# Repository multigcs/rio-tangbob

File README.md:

# TangBOB

cheap universal-board for LinuxCNC-RIO

* W5500
* Level-Shifter (TXS0108E)
* RGB-LED
* Modbus
* I2C - 5V (hope this will work via the level-shifter)

Kicad-Footprint for the TangNano9K:

    https://github.com/jabadiagm/MSXmapper_tn9k/tree/main/kicad/t_mapper.pretty

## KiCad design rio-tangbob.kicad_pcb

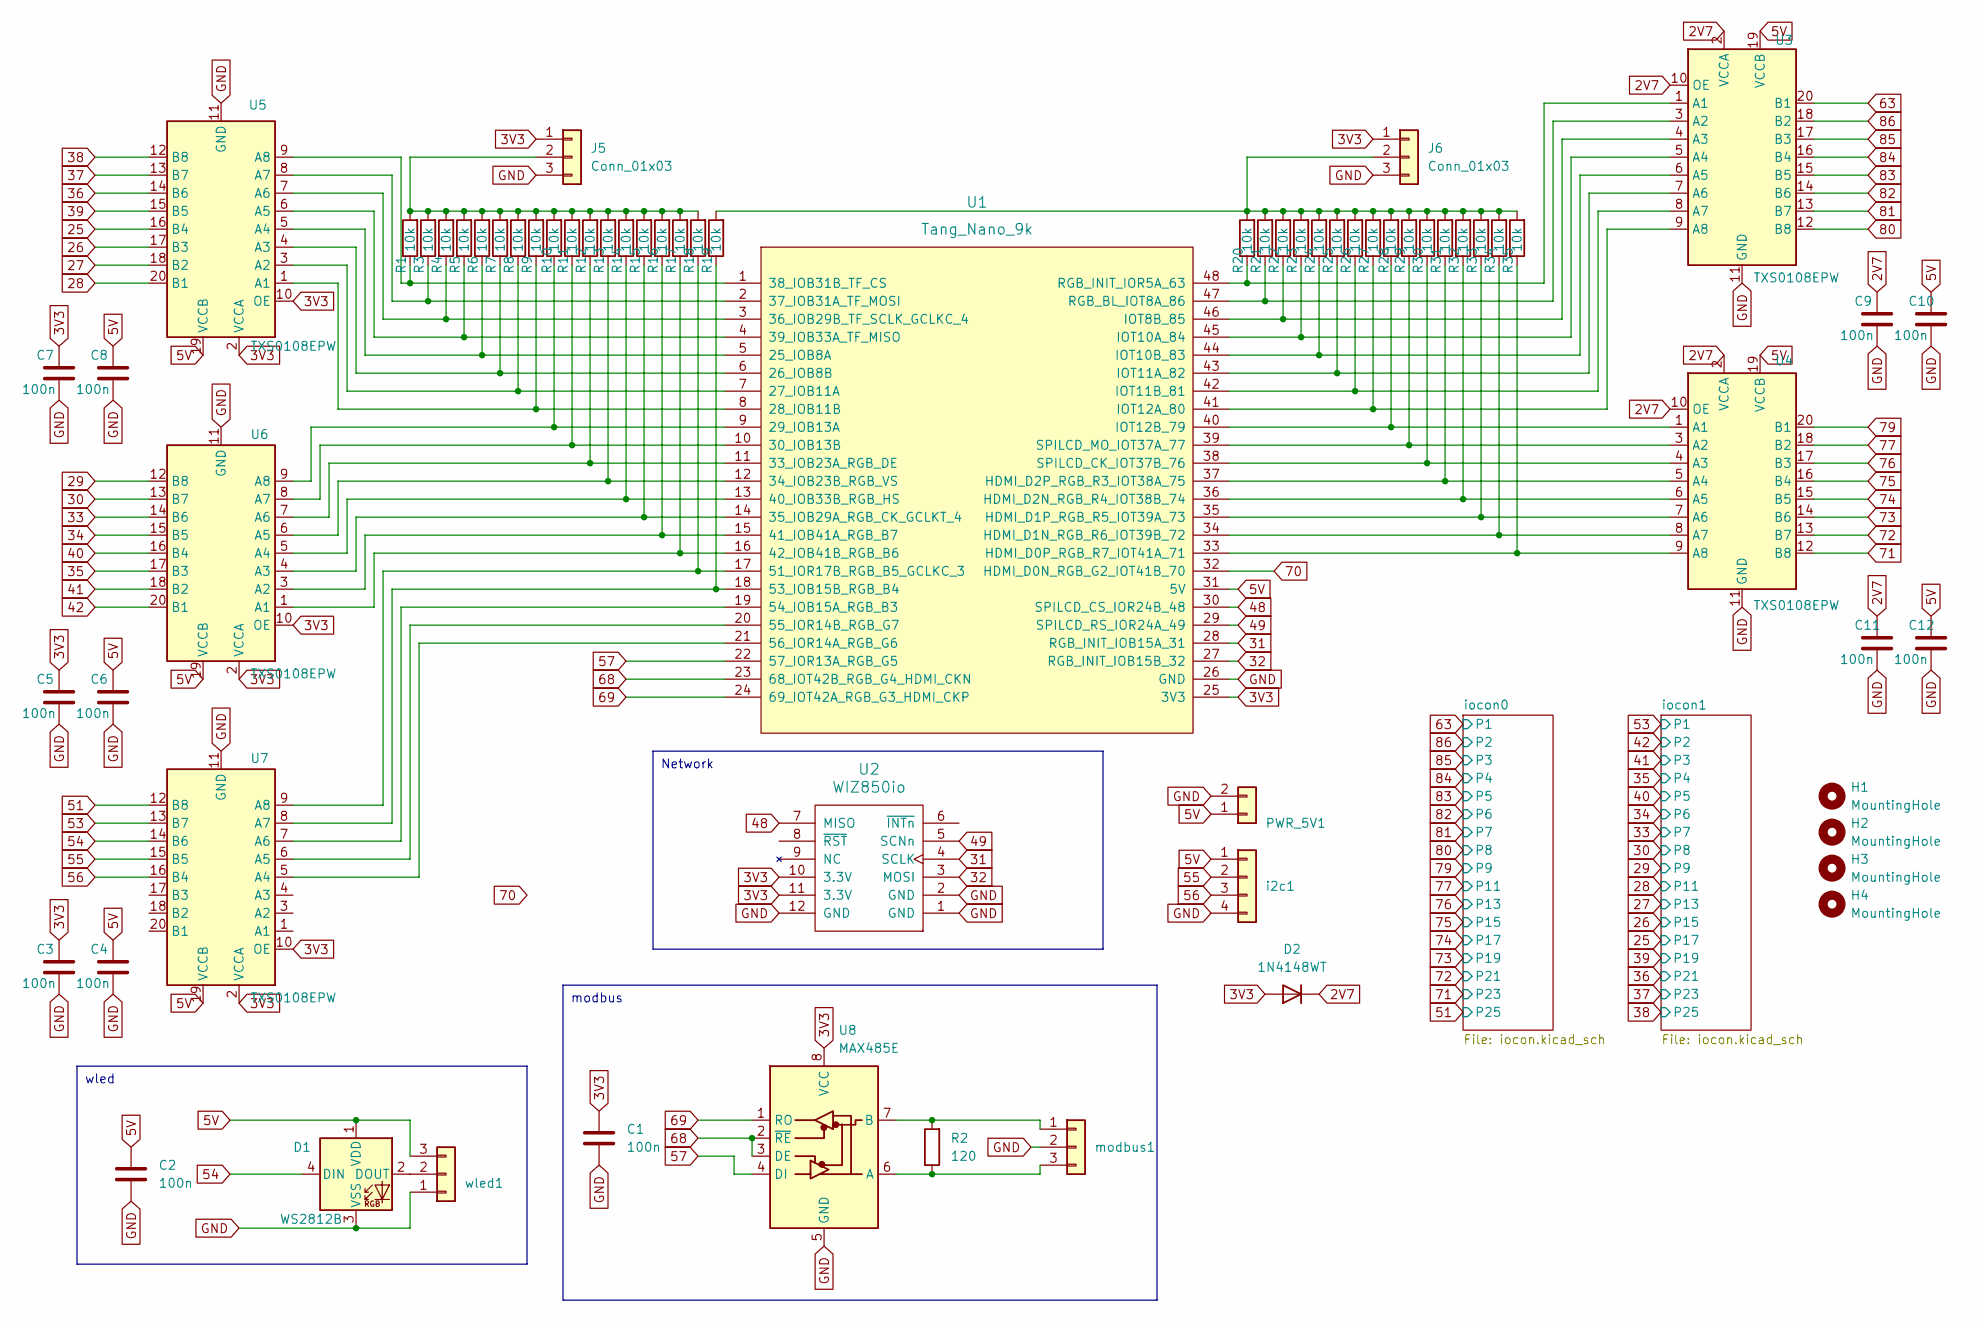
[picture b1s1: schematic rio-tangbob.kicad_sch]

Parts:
C1, C2, C3, C4, C5, C6, C7, C8, C9, C10, C11, C12: 100n; C_1206_3216Metric
D1: WS2812B; LED_WS2812B_PLCC4_5.0x5.0mm_P3.2mm
D2: 1N4148WT; D_SOD-523
H1, H2, H3, H4: MountingHole; MountingHole_3.2mm_M3_DIN965
J5, J6: Conn_01x03; PinHeader_1x03_P2.54mm_Vertical
PWR_5V1: Conn_01x03; JST_XH_B2B-XH-A_1x02_P2.50mm_Vertical
R1, R3, R4, R5, R6, R7, R8, R9, R10, R11, R12, R13, R14, R15, R16, R17, R18, R19, R20, R21, R22, R23, R24, R25, R26, R27, R28, R29, R30, R31, R32, R33, R34, R35: 10k; R_1206_3216Metric
R2: 120; R_1206_3216Metric
U1: Tang_Nano_9k
U2: WIZ850io
U3, U4, U5, U6, U7: TXS0108EPW; TSSOP-20_4.4x6.5mm_P0.65mm
U8: MAX485E; Diodes_SO-8EP
i2c1: Conn_01x03; JST_XH_B4B-XH-A_1x04_P2.50mm_Vertical
modbus1: Conn_01x03; JST_XH_B3B-XH-A_1x03_P2.50mm_Vertical
wled1: Conn_01x03; JST_XH_B3B-XH-A_1x03_P2.50mm_Vertical

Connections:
2V7: C9.1, C11.1, D2.1 (K), U3.2 (VCCA), U3.10 (OE), U4.2 (VCCA), U4.10 (OE)
3V3: C1.1, C3.1, C5.1, C7.1, D2.2 (A), J5.1, J6.1, U1.25 (3V3), U2.10 (3.3V), U2.11 (3.3V), U5.2 (VCCA), U5.10 (OE), U6.2 (VCCA), U6.10 (OE), U7.2 (VCCA), U7.10 (OE), U8.8 (VCC)
5V: C2.1, C4.1, C6.1, C8.1, C10.1, C12.1, D1.1 (VDD), PWR_5V1.1, U1.31 (5V), U3.19 (VCCB), U4.19 (VCCB), U5.19 (VCCB), U6.19 (VCCB), U7.19 (VCCB), i2c1.1, wled1.3; also elsewhere on the board
25: U5.16 (B4); also elsewhere on the board
26: U5.17 (B3); also elsewhere on the board
27: U5.18 (B2); also elsewhere on the board
28: U5.20 (B1); also elsewhere on the board
29: U6.12 (B8); also elsewhere on the board
30: U6.13 (B7); also elsewhere on the board
31: U1.28 (RGB_INIT_IOB15A_31), U2.4 (SCLK)
32: U1.27 (RGB_INIT_IOB15B_32), U2.3 (MOSI)
33: U6.14 (B6); also elsewhere on the board
34: U6.15 (B5); also elsewhere on the board
35: U6.17 (B3); also elsewhere on the board
36: U5.14 (B6); also elsewhere on the board
37: U5.13 (B7); also elsewhere on the board
38: U5.12 (B8); also elsewhere on the board
39: U5.15 (B5); also elsewhere on the board
40: U6.16 (B4); also elsewhere on the board
41: U6.18 (B2); also elsewhere on the board
42: U6.20 (B1); also elsewhere on the board
48: U1.30 (SPILCD_CS_IOR24B_48), U2.7 (MISO)
49: U1.29 (SPILCD_RS_IOR24A_49), U2.5 (SCNn)
51: U7.12 (B8); also elsewhere on the board
53: U7.13 (B7); also elsewhere on the board
54: D1.4 (DIN), U7.14 (B6)
55: U7.15 (B5), i2c1.2
56: U7.16 (B4), i2c1.3
57: U1.22 (57_IOR13A_RGB_G5), U8.4 (DI)
63: U3.20 (B1); also elsewhere on the board
68: U1.23 (68_IOT42B_RGB_G4_HDMI_CKN), U8.2 (~RE), U8.3 (DE)
69: U1.24 (69_IOT42A_RGB_G3_HDMI_CKP), U8.1 (RO)
70: U1.32 (HDMI_D0N_RGB_G2_IOT41B_70)
71: U4.12 (B8); also elsewhere on the board
72: U4.13 (B7); also elsewhere on the board
73: U4.14 (B6); also elsewhere on the board
74: U4.15 (B5); also elsewhere on the board
75: U4.16 (B4); also elsewhere on the board
76: U4.17 (B3); also elsewhere on the board
77: U4.18 (B2); also elsewhere on the board
79: U4.20 (B1); also elsewhere on the board
80: U3.12 (B8); also elsewhere on the board
81: U3.13 (B7); also elsewhere on the board
82: U3.14 (B6); also elsewhere on the board
83: U3.15 (B5); also elsewhere on the board
84: U3.16 (B4); also elsewhere on the board
85: U3.17 (B3); also elsewhere on the board
86: U3.18 (B2); also elsewhere on the board
GND: C1.2, C2.2, C3.2, C4.2, C5.2, C6.2, C7.2, C8.2, C9.2, C10.2, C11.2, C12.2, D1.3 (VSS), J5.3, J6.3, PWR_5V1.2, U1.26 (GND), U2.1 (GND), U2.2 (GND), U2.12 (GND), U3.11 (GND), U4.11 (GND), U5.11 (GND), U6.11 (GND), U7.11 (GND), U8.5 (GND), i2c1.4, modbus1.2, wled1.1; also elsewhere on the board
unnamed: D1.2 (DOUT), wled1.2
unnamed: J5.2, R1.2, R3.2, R4.2, R5.2, R6.2, R7.2, R8.2, R9.2, R10.2, R11.2, R12.2, R13.2, R14.2, R15.2, R16.2, R17.2, R18.2
unnamed: J6.2, R19.2, R20.2, R21.2, R22.2, R23.2, R24.2, R25.2, R26.2, R27.2, R28.2, R29.2, R30.2, R31.2, R32.2, R33.2, R34.2, R35.2
unnamed: R6.1, U1.5 (25_IOB8A), U5.5 (A4)
unnamed: R7.1, U1.6 (26_IOB8B), U5.4 (A3)
unnamed: R8.1, U1.7 (27_IOB11A), U5.3 (A2)
unnamed: R9.1, U1.8 (28_IOB11B), U5.1 (A1)
unnamed: R10.1, U1.9 (29_IOB13A), U6.9 (A8)
unnamed: R11.1, U1.10 (30_IOB13B), U6.8 (A7)
unnamed: R12.1, U1.11 (33_IOB23A_RGB_DE), U6.7 (A6)
unnamed: R13.1, U1.12 (34_IOB23B_RGB_VS), U6.6 (A5)
unnamed: R15.1, U1.14 (35_IOB29A_RGB_CK_GCLKT_4), U6.4 (A3)
unnamed: R4.1, U1.3 (36_IOB29B_TF_SCLK_GCLKC_4), U5.7 (A6)
unnamed: R3.1, U1.2 (37_IOB31A_TF_MOSI), U5.8 (A7)
unnamed: R1.1, U1.1 (38_IOB31B_TF_CS), U5.9 (A8)
unnamed: R5.1, U1.4 (39_IOB33A_TF_MISO), U5.6 (A5)
unnamed: R14.1, U1.13 (40_IOB33B_RGB_HS), U6.5 (A4)
unnamed: R16.1, U1.15 (41_IOB41A_RGB_B7), U6.3 (A2)
unnamed: R17.1, U1.16 (42_IOB41B_RGB_B6), U6.1 (A1)
unnamed: R18.1, U1.17 (51_IOR17B_RGB_B5_GCLKC_3), U7.9 (A8)
unnamed: R19.1, U1.18 (53_IOB15B_RGB_B4), U7.8 (A7)
unnamed: U1.19 (54_IOB15A_RGB_B3), U7.7 (A6)
unnamed: U1.20 (55_IOR14B_RGB_G7), U7.6 (A5)
unnamed: U1.21 (56_IOR14A_RGB_G6), U7.5 (A4)
unnamed: R35.1, U1.33 (HDMI_D0P_RGB_R7_IOT41A_71), U4.9 (A8)
unnamed: R34.1, U1.34 (HDMI_D1N_RGB_R6_IOT39B_72), U4.8 (A7)
unnamed: R33.1, U1.35 (HDMI_D1P_RGB_R5_IOT39A_73), U4.7 (A6)
unnamed: R32.1, U1.36 (HDMI_D2N_RGB_R4_IOT38B_74), U4.6 (A5)
unnamed: R31.1, U1.37 (HDMI_D2P_RGB_R3_IOT38A_75), U4.5 (A4)
unnamed: R22.1, U1.46 (IOT8B_85), U3.4 (A3)
unnamed: R23.1, U1.45 (IOT10A_84), U3.5 (A4)
unnamed: R24.1, U1.44 (IOT10B_83), U3.6 (A5)
unnamed: R25.1, U1.43 (IOT11A_82), U3.7 (A6)
unnamed: R26.1, U1.42 (IOT11B_81), U3.8 (A7)
unnamed: R27.1, U1.41 (IOT12A_80), U3.9 (A8)
unnamed: R28.1, U1.40 (IOT12B_79), U4.1 (A1)
unnamed: R21.1, U1.47 (RGB_BL_IOT8A_86), U3.3 (A2)
unnamed: R20.1, U1.48 (RGB_INIT_IOR5A_63), U3.1 (A1)
unnamed: R30.1, U1.38 (SPILCD_CK_IOT37B_76), U4.4 (A3)
unnamed: R29.1, U1.39 (SPILCD_MO_IOT37A_77), U4.3 (A2)
unnamed: R2.1, U8.6 (A), modbus1.3
unnamed: R2.2, U8.7 (B), modbus1.1

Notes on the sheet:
modbus
wled
Network

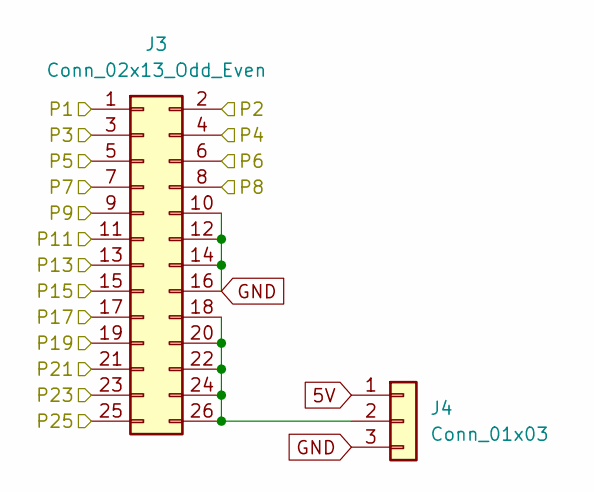
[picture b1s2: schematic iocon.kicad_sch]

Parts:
J3: Conn_02x13_Odd_Even; IDC-Header_2x13_P2.54mm_Vertical
J4: Conn_01x03; PinHeader_1x03_P2.54mm_Vertical

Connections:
5V: J4.1; also elsewhere on the board
25: J3.17; also elsewhere on the board
26: J3.15; also elsewhere on the board
27: J3.13; also elsewhere on the board
28: J3.11; also elsewhere on the board
29: J3.9; also elsewhere on the board
30: J3.8; also elsewhere on the board
33: J3.7; also elsewhere on the board
34: J3.6; also elsewhere on the board
35: J3.4; also elsewhere on the board
36: J3.21; also elsewhere on the board
37: J3.23; also elsewhere on the board
38: J3.25; also elsewhere on the board
39: J3.19; also elsewhere on the board
40: J3.5; also elsewhere on the board
41: J3.3; also elsewhere on the board
42: J3.2; also elsewhere on the board
53: J3.1; also elsewhere on the board
GND: J3.10, J3.12, J3.14, J3.16, J4.3; also elsewhere on the board
unnamed: J3.18, J3.20, J3.22, J3.24, J3.26, J4.2

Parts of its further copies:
J1: Conn_02x13_Odd_Even; IDC-Header_2x13_P2.54mm_Vertical
J2: Conn_01x03; PinHeader_1x03_P2.54mm_Vertical

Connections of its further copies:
5V: J2.1; also elsewhere on the board
51: J1.25; also elsewhere on the board
63: J1.1; also elsewhere on the board
71: J1.23; also elsewhere on the board
72: J1.21; also elsewhere on the board
73: J1.19; also elsewhere on the board
74: J1.17; also elsewhere on the board
75: J1.15; also elsewhere on the board
76: J1.13; also elsewhere on the board
77: J1.11; also elsewhere on the board
79: J1.9; also elsewhere on the board
80: J1.8; also elsewhere on the board
81: J1.7; also elsewhere on the board
82: J1.6; also elsewhere on the board
83: J1.5; also elsewhere on the board
84: J1.4; also elsewhere on the board
85: J1.3; also elsewhere on the board
86: J1.2; also elsewhere on the board
GND: J1.10, J1.12, J1.14, J1.16, J2.3; also elsewhere on the board
unnamed: J1.18, J1.20, J1.22, J1.24, J1.26, J2.2

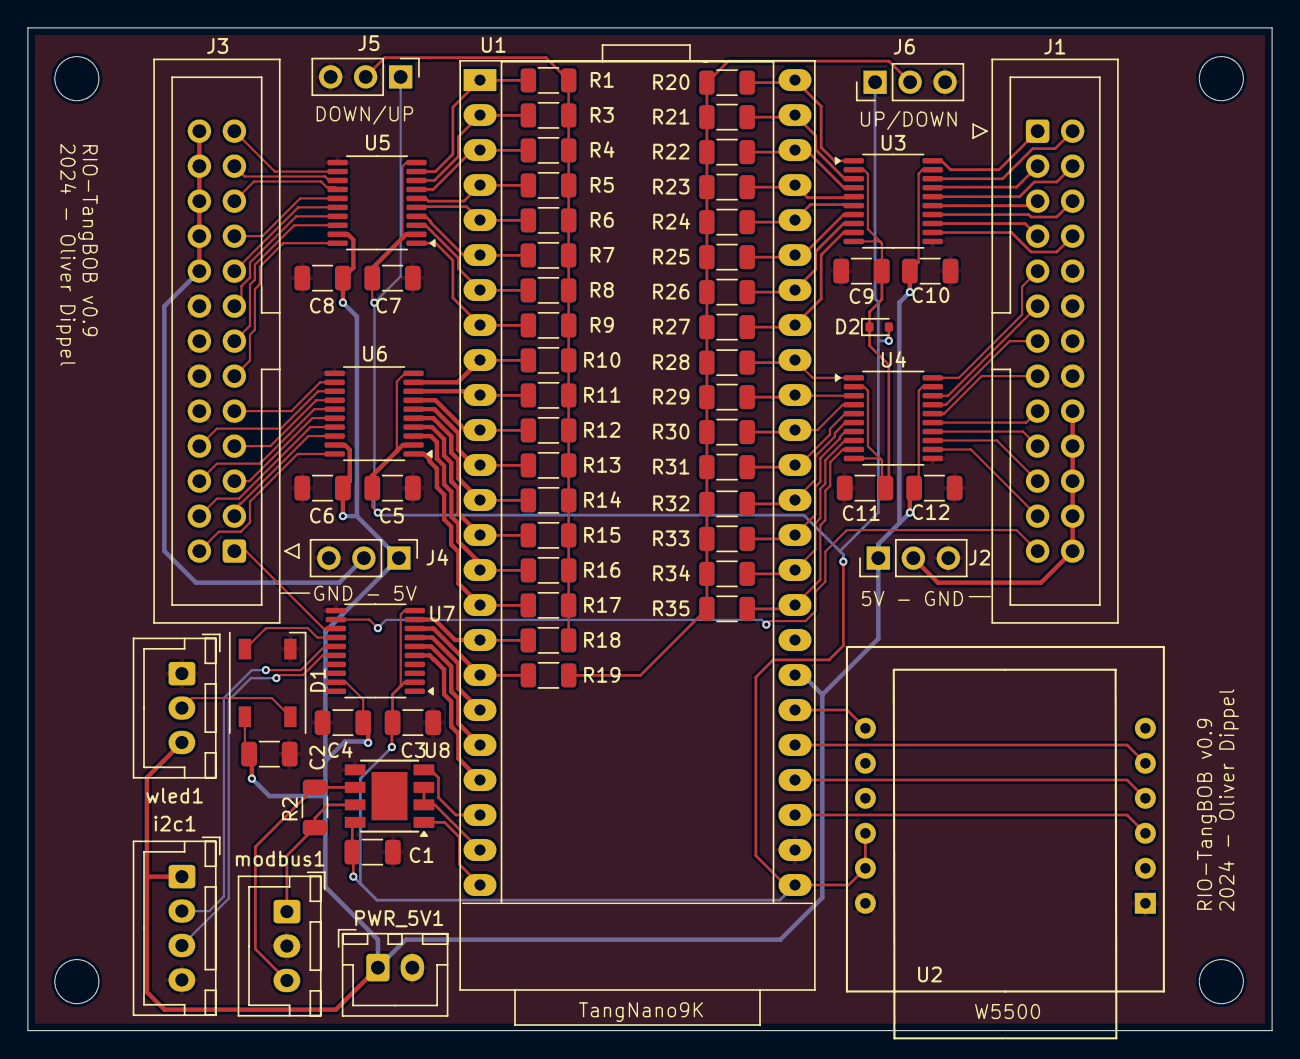
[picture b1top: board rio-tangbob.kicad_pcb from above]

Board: 2 copper layers, 90.3 x 72.8 mm, 71 parts (0 on the bottom side), 92 nets.

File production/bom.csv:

Designator,Footprint,Quantity,Value,LCSC Part #
"C1, C10, C11, C12, C2, C3, C4, C5, C6, C7, C8, C9",1206,12,100n,
D1,LED_WS2812B_PLCC4_5.0x5.0mm_P3.2mm,1,WS2812B,
D2,D_SOD-523,1,1N4148WT,
I2C1,JST_XH_B4B-XH-A_1x04_P2.50mm_Vertical,1,Conn_01x03,
"J1, J3",IDC-Header_2x13_P2.54mm_Vertical,2,Conn_02x13_Odd_Even,
"J2, J4, J5, J6",PinHeader_1x03_P2.54mm_Vertical,4,Conn_01x03,
"MODBUS1, WLED1",JST_XH_B3B-XH-A_1x03_P2.50mm_Vertical,2,Conn_01x03,
PWR_5V1,JST_XH_B2B-XH-A_1x02_P2.50mm_Vertical,1,Conn_01x03,
"R1, R10, R11, R12, R13, R14, R15, R16, R17, R18, R19, R20, R21, R22, R23, R24, R25, R26, R27, R28, R29, R3, R30, R31, R32, R33, R34, R35, R4, R5, R6, R7, R8, R9",1206,34,10k,
R2,1206,1,120,
U1,Tang_Nano_9k,1,Tang_Nano_9k,
U2,WIZ850io,1,WIZ850io,
"U3, U4, U5, U6, U7",TSSOP-20_4.4x6.5mm_P0.65mm,5,TXS0108EPW,
U8,Diodes_SO-8EP,1,MAX485E,

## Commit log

2024-08-18 initial release
2024-08-18 adding pdf schematics
2024-10-09 set U3+U4 voltage to ~2.7V
2025-04-01 adding fabrication files
2026-01-29 Update README to remove testing disclaimer
    Removed the 'NOT ALL TESTED' note from README.
